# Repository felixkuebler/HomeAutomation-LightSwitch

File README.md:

# Introduction
Due to the growing demand of iot devices for home automation this project presents an cheap, easy to use and "open source" alternative to brand Products such as Phillips Hue. Based on the ESP8266-12E, a small WiFi enabled chipset, these devices can be retrofitted in a variety of devices such as light switches, motor controllers and more.

Each home automation node will access your local wifi network and is configurable through a webpage hosted locally on the device itsself. Your network needs to provide a [mqtt](https://pagefault.blog/2017/03/02/using-local-mqtt-broker-for-cloud-and-interprocess-communication/) broker to enable communication between nodes thus enabling its full functionality. An easy to use webinterface as well as a mqtt broker is provided by [Openhab](https://www.openhab.org/).

# Light Switch
The light switch module is an small embedded device that can be integrated in your 220 VAC power grid without any special adaptations. Powered by the [HLK-PM01](http://www.hlktech.net/product_detail.php?ProId=54) this module provides two digital inputs as well as two solid state relay outputs. Each input and output can be assigned and modified individually via the local web interface. Due to its small form factor it can easily be fitted behind any flush-mounted box with a min. depth of 41mm.

![[light switch render]](Hardware/Electronics/Render/LightSwitch_3D.jpg)
![[light switch render]](Hardware/Mechanics/Render/LightSwitch_3D.jpg)

The current versions can be found here:
* [Version 1.0](../../tree/Version1.0)

# License
This work is property of Felix Kübler and is licensed under the
<a rel="license" href="http://creativecommons.org/licenses/by-nc/4.0/">Creative Commons Attribution-NonCommercial 4.0 International License</a>.

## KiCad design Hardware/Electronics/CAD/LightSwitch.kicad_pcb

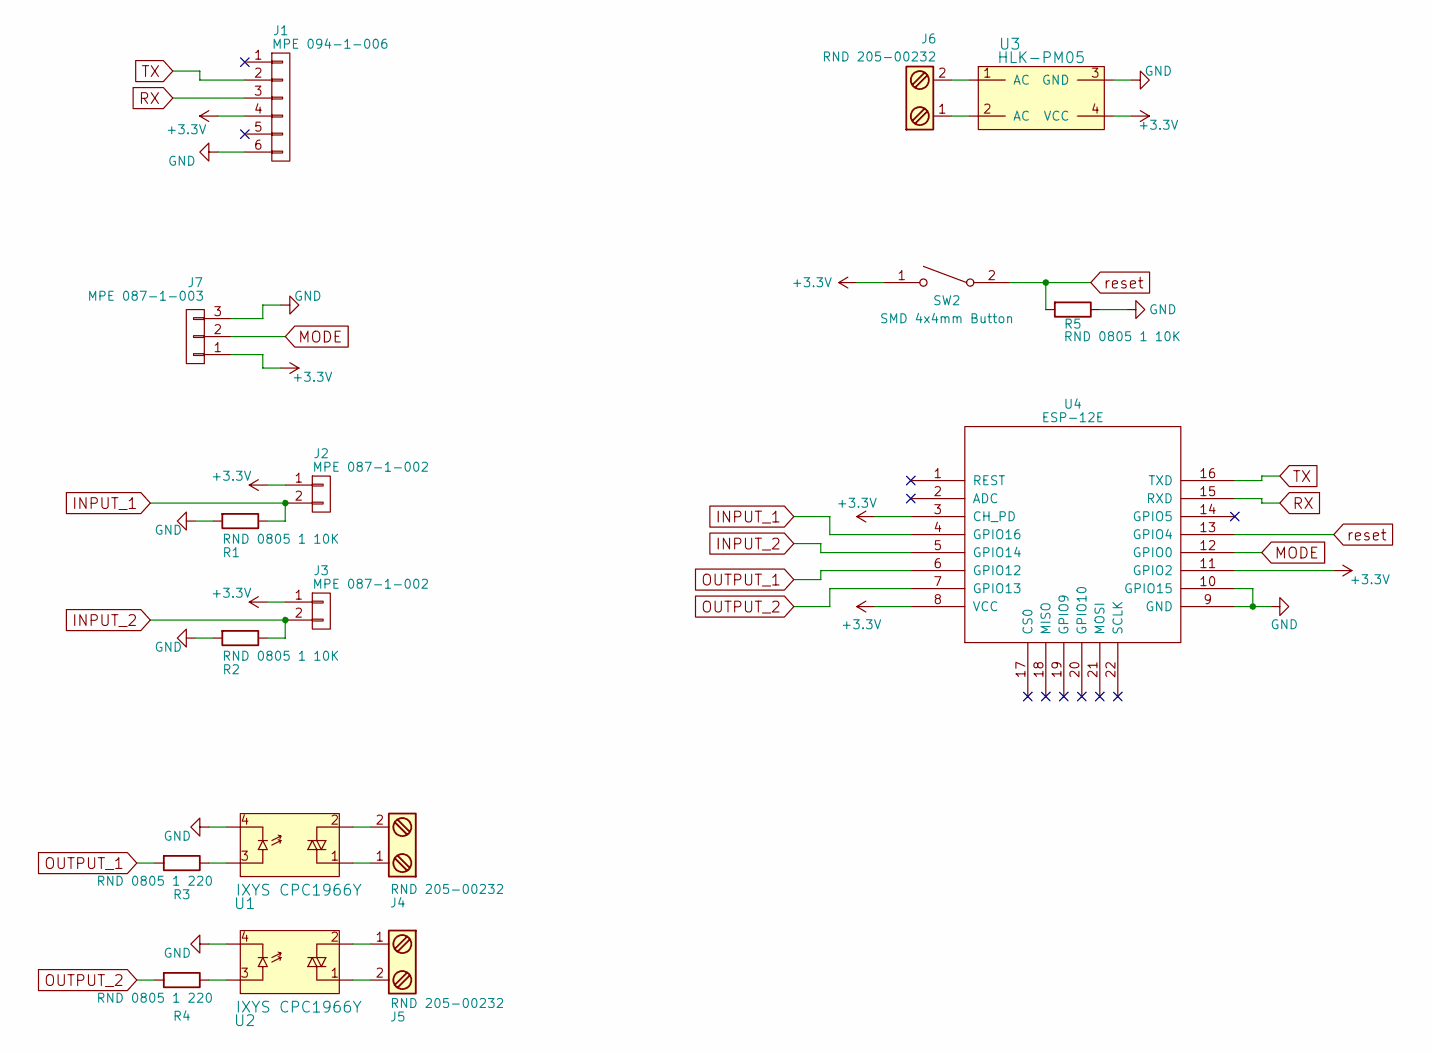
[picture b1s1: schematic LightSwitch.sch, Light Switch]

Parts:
J1: MPE 094-1-006; Pin_Header_Straight_1x06_Pitch2.54mm
J2, J3: MPE 087-1-002; Pin_Header_Straight_1x02_Pitch2.54mm
J4, J5, J6: RND 205-00232; Terminal_1x2_2.54mm
J7: MPE 087-1-003; Pin_Header_Straight_1x03_Pitch2.54mm
R1, R2, R5: RND 0805 1 10K; R_0805
R3, R4: RND 0805 1 220; R_0805
SW2: SMD 4x4mm Button; SW_SPST_TL3342
U1, U2: IXYS CPC1966Y; CPC1966Y
U3: HLK-PM05; HLK-PM01
U4: ESP-12E; ESP-12E_SMD

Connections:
+3V3: J1.4, J2.1, J3.1, J7.1, SW2.1, U3.4 (VCC), U4.3 (CH_PD), U4.8 (VCC), U4.11 (GPIO2)
GND: J1.6, J7.3, R1.2, R2.2, R5.1, U1.4, U2.4, U3.3 (GND), U4.9 (GND), U4.10 (GPIO15)
INPUT_1: J2.2, R1.1, U4.4 (GPIO16)
INPUT_2: J3.2, R2.1, U4.5 (GPIO14)
MODE: J7.2, U4.12 (GPIO0)
unnamed: J4.1, U1.1
unnamed: J4.2, U1.2
unnamed: J5.1, U2.2
unnamed: J5.2, U2.1
unnamed: J6.1, U3.2 (AC)
unnamed: J6.2, U3.1 (AC)
unnamed: R3.1, U1.3
unnamed: R4.1, U2.3
OUTPUT_1: R3.2, U4.6 (GPIO12)
OUTPUT_2: R4.2, U4.7 (GPIO13)
RX: J1.3, U4.15 (RXD)
TX: J1.2, U4.16 (TXD)
reset: R5.2, SW2.2, U4.13 (GPIO4)

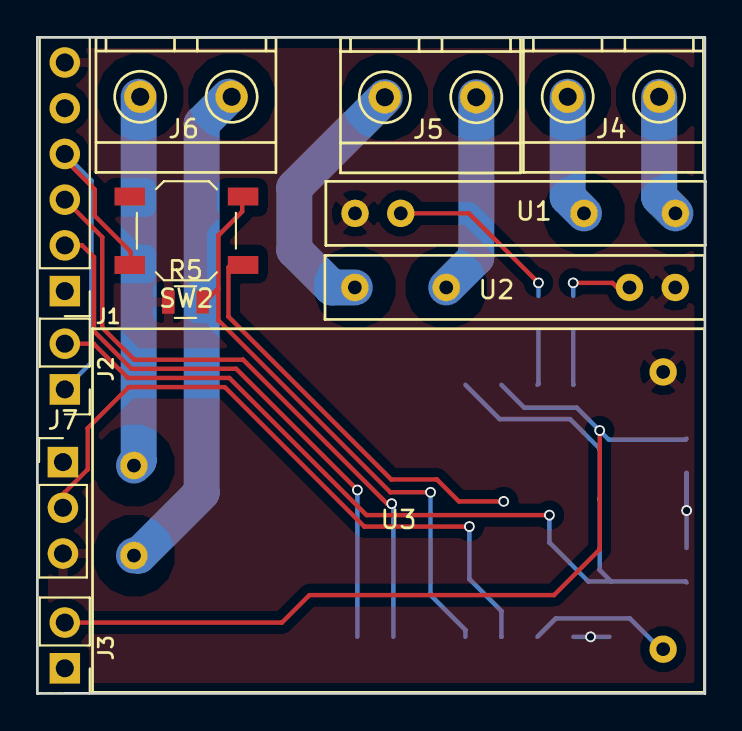
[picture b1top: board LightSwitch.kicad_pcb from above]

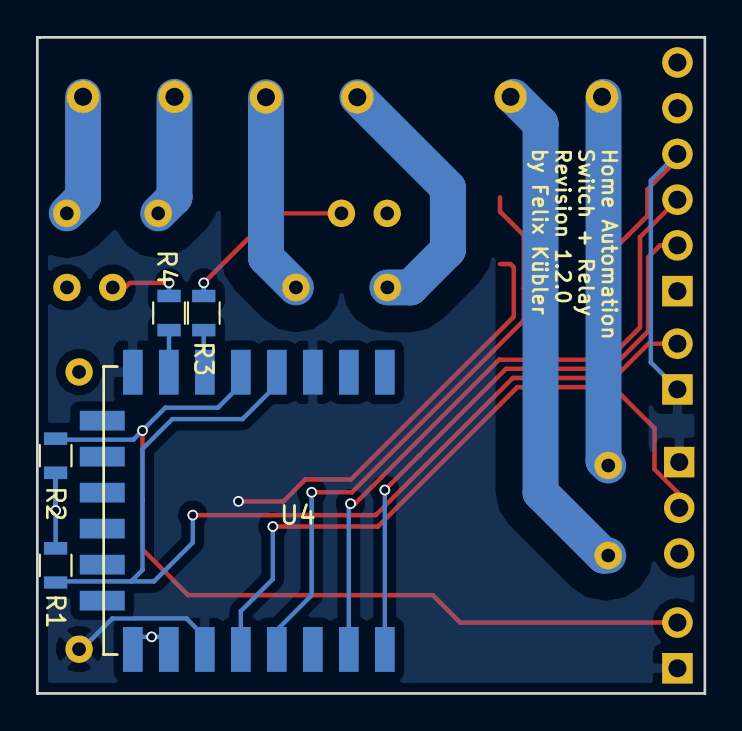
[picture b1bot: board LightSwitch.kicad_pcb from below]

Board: 2 copper layers, 37.1 x 36.4 mm, 17 parts (5 on the bottom side), 18 nets.

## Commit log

2018-02-15 light switch single repo setup
2018-02-18 updated files
2018-02-23 web updater implemented
2018-03-20 direct webrequest control implemented
2018-03-23 specification added
2018-03-23 cleanup
2018-03-24 new software file structure
2018-03-24 introduction of basic setup files
2018-04-08 kicad linkage fix
2018-04-15 3d model improvement and default parts
2018-06-03 new renderings
2018-09-03 test assembly
2018-09-03 library linkage fix
2018-09-05 terminal footprints
2018-09-20 documentation
2018-09-23 housing for pcb
2018-09-23 reedit
2019-02-21 housing concept
2020-04-07 comment cleanup
2022-10-22 update wiki file and rename to README
2022-10-22 rename Specifications to Datasheets
2022-10-23 rename software source and move tests in source
2022-10-23 rename tests
